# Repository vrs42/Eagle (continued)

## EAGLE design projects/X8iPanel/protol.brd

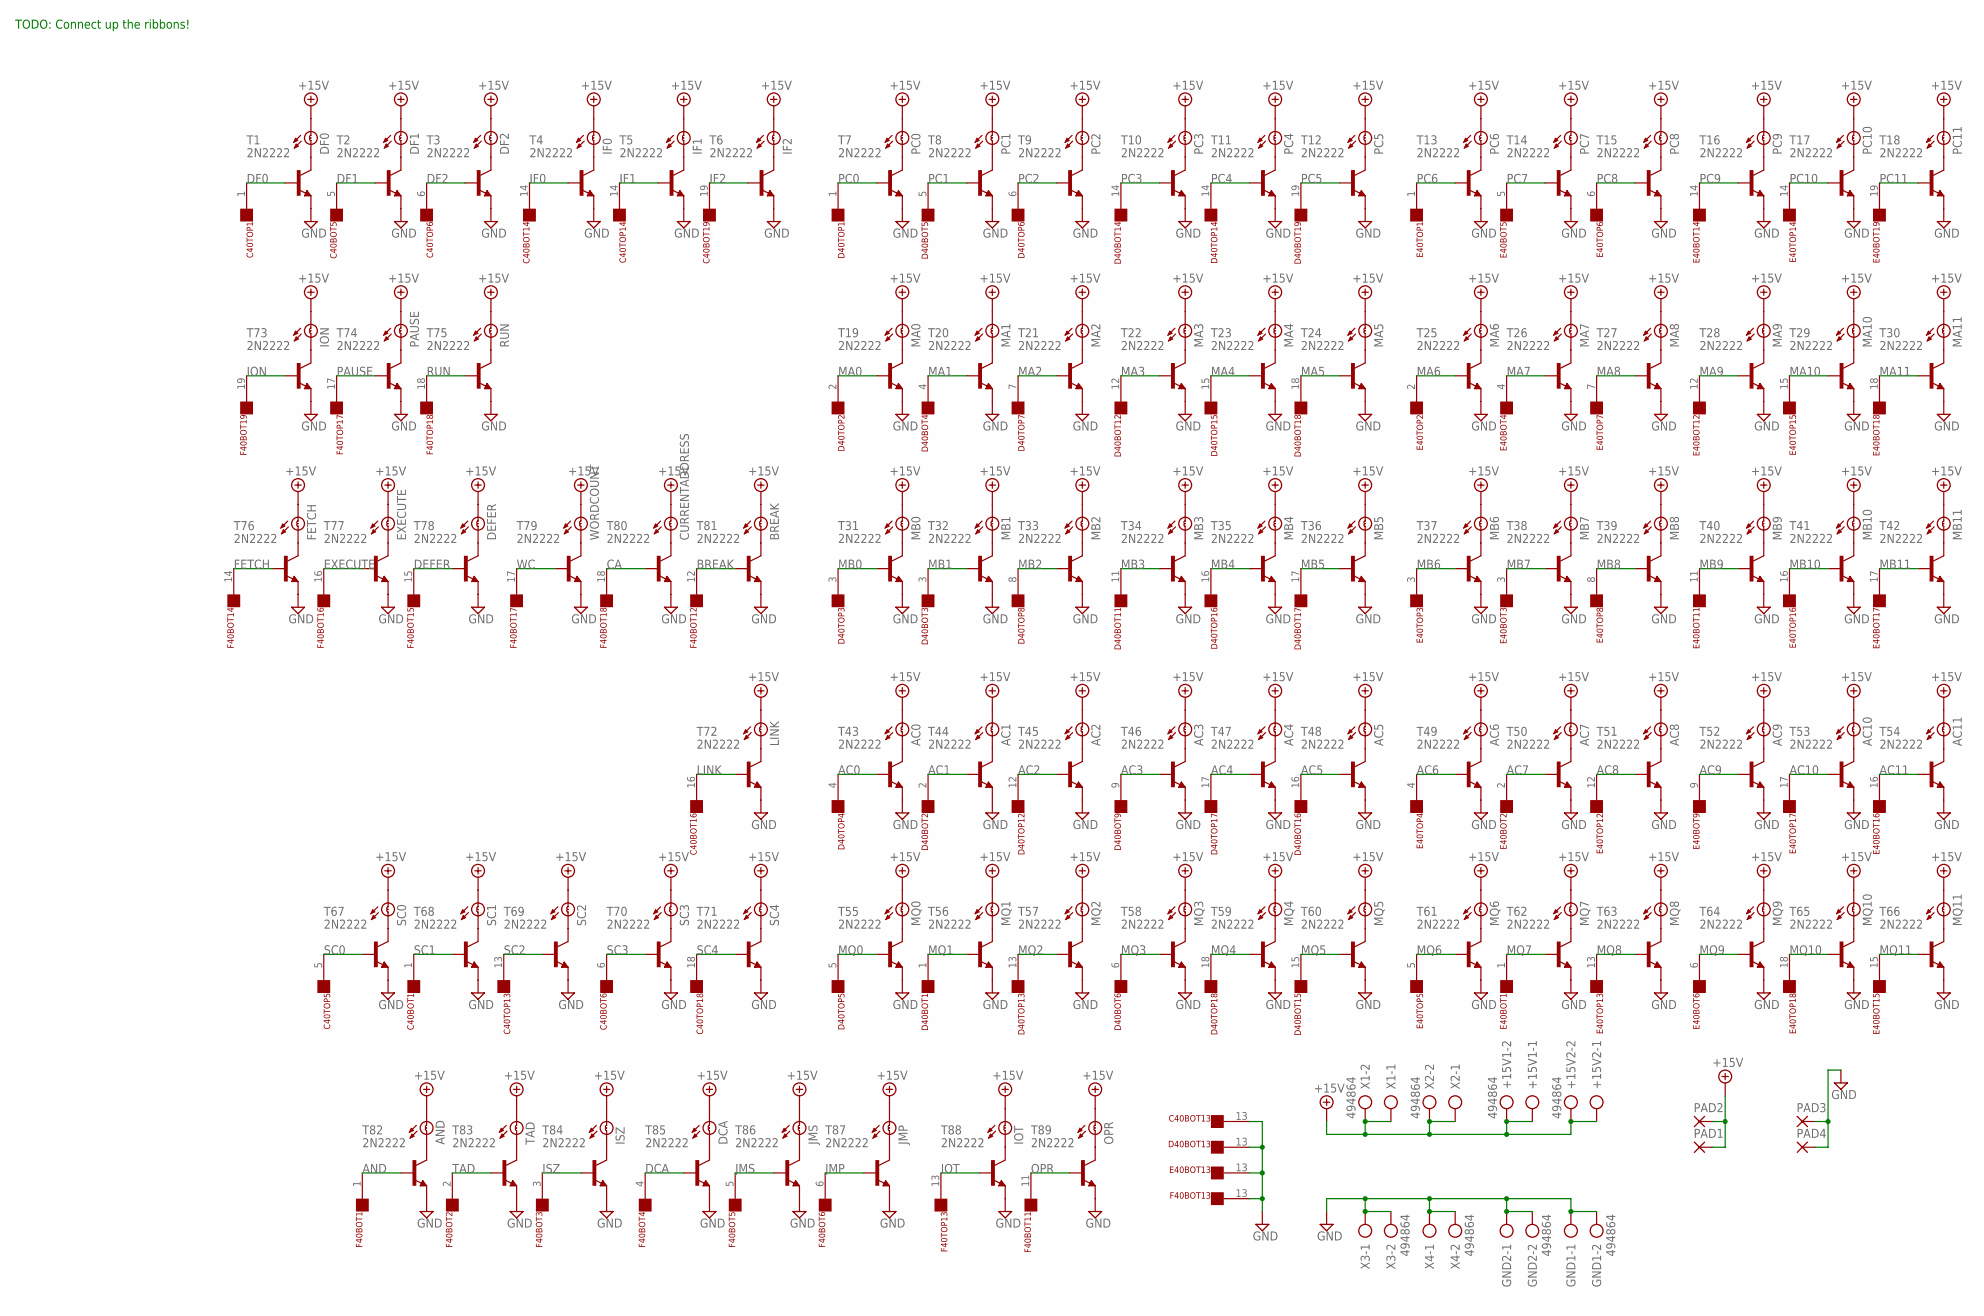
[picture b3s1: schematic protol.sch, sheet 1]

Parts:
+15V1, +15V2: 494864; AK500/2
AC0, AC1, AC2, AC3, AC4, AC5, AC6, AC7, AC8, AC9, AC10, AC11: BULB
AND: BULB
BREAK: BULB
C40BOT, C40TOP: FLEX19
CURRENTADDRESS: BULB
D40BOT, D40TOP: FLEX19
DCA: BULB
DEFER: BULB
DF0, DF1, DF2: BULB
E40BOT, E40TOP: FLEX19
EXECUTE: BULB
F40BOT, F40TOP: FLEX19
FETCH: BULB
GND1, GND2: 494864; AK500/2
IF0, IF1, IF2: BULB
ION: BULB
IOT: BULB
ISZ: BULB
JMP: BULB
JMS: BULB
LINK: BULB
MA0, MA1, MA2, MA3, MA4, MA5, MA6, MA7, MA8, MA9, MA10, MA11: BULB
MB0, MB1, MB2, MB3, MB4, MB5, MB6, MB7, MB8, MB9, MB10, MB11: BULB
MQ0, MQ1, MQ2, MQ3, MQ4, MQ5, MQ6, MQ7, MQ8, MQ9, MQ10, MQ11: BULB
OPR: BULB
PAD1, PAD2, PAD3, PAD4: 2,54/0,8
PAUSE: BULB
PC0, PC1, PC2, PC3, PC4, PC5, PC6, PC7, PC8, PC9, PC10, PC11: BULB
RUN: BULB
SC0, SC1, SC2, SC3, SC4: BULB
T1, T2, T3, T4, T5, T6, T7, T8, T9, T10, T11, T12, T13, T14, T15, T16, T17, T18, T19, T20, T21, T22, T23, T24, T25, T26, T27, T28, T29, T30, T31, T32, T33, T34, T35, T36, T37, T38, T39, T40, T41, T42, T43, T44, T45, T46, T47, T48, T49, T50, T51, T52, T53, T54, T55, T56, T57, T58, T59, T60, T61, T62, T63, T64, T65, T66, T67, T68, T69, T70, T71, T72, T73, T74, T75, T76, T77, T78, T79, T80, T81, T82, T83, T84, T85, T86, T87, T88, T89: 2N2222; TO92
TAD: BULB
WORDCOUNT: BULB
X1, X2, X3, X4: 494864; AK500/2

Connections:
+15V: +15V1.1, +15V1.2, +15V2.1, +15V2.2, AC0.A, AC1.A, AC2.A, AC3.A, AC4.A, AC5.A, AC6.A, AC7.A, AC8.A, AC9.A, AC10.A, AC11.A, AND.A, BREAK.A, CURRENTADDRESS.A, DCA.A, DEFER.A, DF0.A, DF1.A, DF2.A, EXECUTE.A, FETCH.A, IF0.A, IF1.A, IF2.A, ION.A, IOT.A, ISZ.A, JMP.A, JMS.A, LINK.A, MA0.A, MA1.A, MA2.A, MA3.A, MA4.A, MA5.A, MA6.A, MA7.A, MA8.A, MA9.A, MA10.A, MA11.A, MB0.A, MB1.A, MB2.A, MB3.A, MB4.A, MB5.A, MB6.A, MB7.A, MB8.A, MB9.A, MB10.A, MB11.A, MQ0.A, MQ1.A, MQ2.A, MQ3.A, MQ4.A, MQ5.A, MQ6.A, MQ7.A, MQ8.A, MQ9.A, MQ10.A, MQ11.A, OPR.A, PAD1.1, PAD2.1, PAUSE.A, PC0.A, PC1.A, PC2.A, PC3.A, PC4.A, PC5.A, PC6.A, PC7.A, PC8.A, PC9.A, PC10.A, PC11.A, RUN.A, SC0.A, SC1.A, SC2.A, SC3.A, SC4.A, TAD.A, WORDCOUNT.A, X1.1, X1.2, X2.1, X2.2
AC0: D40TOP.4, T43.2 (B); also elsewhere on the board
AC1: D40BOT.2, T44.2 (B); also elsewhere on the board
AC2: D40TOP.12, T45.2 (B); also elsewhere on the board
AC3: D40BOT.9, T46.2 (B); also elsewhere on the board
AC4: D40TOP.17, T47.2 (B); also elsewhere on the board
AC5: D40BOT.16, T48.2 (B); also elsewhere on the board
AC6: E40TOP.4, T49.2 (B); also elsewhere on the board
AC7: E40BOT.2, T50.2 (B); also elsewhere on the board
AC8: E40TOP.12, T51.2 (B); also elsewhere on the board
AC9: E40BOT.9, T52.2 (B); also elsewhere on the board
AC10: E40TOP.17, T53.2 (B); also elsewhere on the board
AC11: E40BOT.16, T54.2 (B); also elsewhere on the board
AND: F40BOT.1, T82.2 (B); also elsewhere on the board
BREAK: F40BOT.12, T81.2 (B); also elsewhere on the board
CA: F40BOT.18, T80.2 (B); also elsewhere on the board
DCA: F40BOT.4, T85.2 (B); also elsewhere on the board
DEFER: F40BOT.15, T78.2 (B); also elsewhere on the board
DF0: C40TOP.1, T1.2 (B); also elsewhere on the board
DF1: C40BOT.5, T2.2 (B); also elsewhere on the board
DF2: C40TOP.6, T3.2 (B); also elsewhere on the board
EXECUTE: F40BOT.16, T77.2 (B); also elsewhere on the board
FETCH: F40BOT.14, T76.2 (B); also elsewhere on the board
GND: C40BOT.13, D40BOT.13, E40BOT.13, F40BOT.13, GND1.1, GND1.2, GND2.1, GND2.2, PAD3.1, PAD4.1, T1.1 (E), T2.1 (E), T3.1 (E), T4.1 (E), T5.1 (E), T6.1 (E), T7.1 (E), T8.1 (E), T9.1 (E), T10.1 (E), T11.1 (E), T12.1 (E), T13.1 (E), T14.1 (E), T15.1 (E), T16.1 (E), T17.1 (E), T18.1 (E), T19.1 (E), T20.1 (E), T21.1 (E), T22.1 (E), T23.1 (E), T24.1 (E), T25.1 (E), T26.1 (E), T27.1 (E), T28.1 (E), T29.1 (E), T30.1 (E), T31.1 (E), T32.1 (E), T33.1 (E), T34.1 (E), T35.1 (E), T36.1 (E), T37.1 (E), T38.1 (E), T39.1 (E), T40.1 (E), T41.1 (E), T42.1 (E), T43.1 (E), T44.1 (E), T45.1 (E), T46.1 (E), T47.1 (E), T48.1 (E), T49.1 (E), T50.1 (E), T51.1 (E), T52.1 (E), T53.1 (E), T54.1 (E), T55.1 (E), T56.1 (E), T57.1 (E), T58.1 (E), T59.1 (E), T60.1 (E), T61.1 (E), T62.1 (E), T63.1 (E), T64.1 (E), T65.1 (E), T66.1 (E), T67.1 (E), T68.1 (E), T69.1 (E), T70.1 (E), T71.1 (E), T72.1 (E), T73.1 (E), T74.1 (E), T75.1 (E), T76.1 (E), T77.1 (E), T78.1 (E), T79.1 (E), T80.1 (E), T81.1 (E), T82.1 (E), T83.1 (E), T84.1 (E), T85.1 (E), T86.1 (E), T87.1 (E), T88.1 (E), T89.1 (E), X3.1, X3.2, X4.1, X4.2; also elsewhere on the board
IF0: C40BOT.14, T4.2 (B); also elsewhere on the board
IF1: C40TOP.14, T5.2 (B); also elsewhere on the board
IF2: C40BOT.19, T6.2 (B); also elsewhere on the board
ION: F40BOT.19, T73.2 (B); also elsewhere on the board
IOT: F40TOP.13, T88.2 (B); also elsewhere on the board
ISZ: F40BOT.3, T84.2 (B); also elsewhere on the board
JMP: F40BOT.6, T87.2 (B); also elsewhere on the board
JMS: F40BOT.5, T86.2 (B); also elsewhere on the board
LINK: C40BOT.16, T72.2 (B); also elsewhere on the board
MA0: D40TOP.2, T19.2 (B); also elsewhere on the board
MA1: D40BOT.4, T20.2 (B); also elsewhere on the board
MA2: D40TOP.7, T21.2 (B); also elsewhere on the board
MA3: D40BOT.12, T22.2 (B); also elsewhere on the board
MA4: D40TOP.15, T23.2 (B); also elsewhere on the board
MA5: D40BOT.18, T24.2 (B); also elsewhere on the board
MA6: E40TOP.2, T25.2 (B); also elsewhere on the board
MA7: E40BOT.4, T26.2 (B); also elsewhere on the board
MA8: E40TOP.7, T27.2 (B); also elsewhere on the board
MA9: E40BOT.12, T28.2 (B); also elsewhere on the board
MA10: E40TOP.15, T29.2 (B); also elsewhere on the board
MA11: E40BOT.18, T30.2 (B); also elsewhere on the board
MB0: D40TOP.3, T31.2 (B); also elsewhere on the board
MB1: D40BOT.3, T32.2 (B); also elsewhere on the board
MB2: D40TOP.8, T33.2 (B); also elsewhere on the board
MB3: D40BOT.11, T34.2 (B); also elsewhere on the board
MB4: D40TOP.16, T35.2 (B); also elsewhere on the board
MB5: D40BOT.17, T36.2 (B); also elsewhere on the board
MB6: E40TOP.3, T37.2 (B); also elsewhere on the board
MB7: E40BOT.3, T38.2 (B); also elsewhere on the board
MB8: E40TOP.8, T39.2 (B); also elsewhere on the board
MB9: E40BOT.11, T40.2 (B); also elsewhere on the board
MB10: E40TOP.16, T41.2 (B); also elsewhere on the board
MB11: E40BOT.17, T42.2 (B); also elsewhere on the board
MQ0: D40TOP.5, T55.2 (B); also elsewhere on the board
MQ1: D40BOT.1, T56.2 (B); also elsewhere on the board
MQ2: D40TOP.13, T57.2 (B); also elsewhere on the board
MQ3: D40BOT.6, T58.2 (B); also elsewhere on the board
MQ4: D40TOP.18, T59.2 (B); also elsewhere on the board
MQ5: D40BOT.15, T60.2 (B); also elsewhere on the board
MQ6: E40TOP.5, T61.2 (B); also elsewhere on the board
MQ7: E40BOT.1, T62.2 (B); also elsewhere on the board
MQ8: E40TOP.13, T63.2 (B); also elsewhere on the board
MQ9: E40BOT.6, T64.2 (B); also elsewhere on the board
MQ10: E40TOP.18, T65.2 (B); also elsewhere on the board
MQ11: E40BOT.15, T66.2 (B); also elsewhere on the board
unnamed: DF0.B, T1.3 (C)
unnamed: DF1.B, T2.3 (C)
unnamed: DF2.B, T3.3 (C)
unnamed: IF0.B, T4.3 (C)
unnamed: IF1.B, T5.3 (C)
unnamed: IF2.B, T6.3 (C)
unnamed: PC0.B, T7.3 (C)
unnamed: PC1.B, T8.3 (C)
unnamed: PC2.B, T9.3 (C)
unnamed: PC3.B, T10.3 (C)
unnamed: PC4.B, T11.3 (C)
unnamed: PC5.B, T12.3 (C)
unnamed: PC6.B, T13.3 (C)
unnamed: PC7.B, T14.3 (C)
unnamed: PC8.B, T15.3 (C)
unnamed: PC9.B, T16.3 (C)
unnamed: PC10.B, T17.3 (C)
unnamed: PC11.B, T18.3 (C)
unnamed: MA0.B, T19.3 (C)
unnamed: MA1.B, T20.3 (C)
unnamed: MA2.B, T21.3 (C)
unnamed: MA3.B, T22.3 (C)
unnamed: MA4.B, T23.3 (C)
unnamed: MA5.B, T24.3 (C)
unnamed: MA6.B, T25.3 (C)
unnamed: MA7.B, T26.3 (C)
unnamed: MA8.B, T27.3 (C)
unnamed: MA9.B, T28.3 (C)
unnamed: MA10.B, T29.3 (C)
unnamed: MA11.B, T30.3 (C)
unnamed: MB0.B, T31.3 (C)
unnamed: MB1.B, T32.3 (C)
unnamed: MB2.B, T33.3 (C)
unnamed: MB3.B, T34.3 (C)
unnamed: MB4.B, T35.3 (C)
unnamed: MB5.B, T36.3 (C)
unnamed: MB6.B, T37.3 (C)
unnamed: MB7.B, T38.3 (C)
unnamed: MB8.B, T39.3 (C)
unnamed: MB9.B, T40.3 (C)
unnamed: MB10.B, T41.3 (C)
unnamed: MB11.B, T42.3 (C)
unnamed: AC0.B, T43.3 (C)
unnamed: AC1.B, T44.3 (C)
unnamed: AC2.B, T45.3 (C)
unnamed: AC3.B, T46.3 (C)
unnamed: AC4.B, T47.3 (C)
unnamed: AC5.B, T48.3 (C)
unnamed: AC6.B, T49.3 (C)
unnamed: AC7.B, T50.3 (C)
unnamed: AC8.B, T51.3 (C)
unnamed: AC9.B, T52.3 (C)
unnamed: AC10.B, T53.3 (C)
unnamed: AC11.B, T54.3 (C)
unnamed: MQ0.B, T55.3 (C)
unnamed: MQ1.B, T56.3 (C)
unnamed: MQ2.B, T57.3 (C)
unnamed: MQ3.B, T58.3 (C)
unnamed: MQ4.B, T59.3 (C)
unnamed: MQ5.B, T60.3 (C)
unnamed: MQ6.B, T61.3 (C)
unnamed: MQ7.B, T62.3 (C)
unnamed: MQ8.B, T63.3 (C)
unnamed: MQ9.B, T64.3 (C)
unnamed: MQ10.B, T65.3 (C)
unnamed: MQ11.B, T66.3 (C)
unnamed: SC0.B, T67.3 (C)
unnamed: SC1.B, T68.3 (C)
unnamed: SC2.B, T69.3 (C)
unnamed: SC3.B, T70.3 (C)
unnamed: SC4.B, T71.3 (C)
unnamed: LINK.B, T72.3 (C)
unnamed: ION.B, T73.3 (C)
unnamed: PAUSE.B, T74.3 (C)
unnamed: RUN.B, T75.3 (C)
unnamed: FETCH.B, T76.3 (C)
unnamed: EXECUTE.B, T77.3 (C)
unnamed: DEFER.B, T78.3 (C)
unnamed: T79.3 (C), WORDCOUNT.B
unnamed: CURRENTADDRESS.B, T80.3 (C)
unnamed: BREAK.B, T81.3 (C)
unnamed: AND.B, T82.3 (C)
unnamed: T83.3 (C), TAD.B
unnamed: ISZ.B, T84.3 (C)
unnamed: DCA.B, T85.3 (C)
unnamed: JMS.B, T86.3 (C)
unnamed: JMP.B, T87.3 (C)
unnamed: IOT.B, T88.3 (C)
unnamed: OPR.B, T89.3 (C)
OPR: F40BOT.11, T89.2 (B); also elsewhere on the board
PAUSE: F40TOP.17, T74.2 (B); also elsewhere on the board
PC0: D40TOP.1, T7.2 (B); also elsewhere on the board
PC1: D40BOT.5, T8.2 (B); also elsewhere on the board
PC2: D40TOP.6, T9.2 (B); also elsewhere on the board
PC3: D40BOT.14, T10.2 (B); also elsewhere on the board
PC4: D40TOP.14, T11.2 (B); also elsewhere on the board
PC5: D40BOT.19, T12.2 (B); also elsewhere on the board
PC6: E40TOP.1, T13.2 (B); also elsewhere on the board
PC7: E40BOT.5, T14.2 (B); also elsewhere on the board
PC8: E40TOP.6, T15.2 (B); also elsewhere on the board
PC9: E40BOT.14, T16.2 (B); also elsewhere on the board
PC10: E40TOP.14, T17.2 (B); also elsewhere on the board
PC11: E40BOT.19, T18.2 (B); also elsewhere on the board
RUN: F40TOP.18, T75.2 (B); also elsewhere on the board
SC0: C40TOP.5, T67.2 (B); also elsewhere on the board
SC1: C40BOT.1, T68.2 (B); also elsewhere on the board
SC2: C40TOP.13, T69.2 (B); also elsewhere on the board
SC3: C40BOT.6, T70.2 (B); also elsewhere on the board
SC4: C40TOP.18, T71.2 (B); also elsewhere on the board
TAD: F40BOT.2, T83.2 (B); also elsewhere on the board
WC: F40BOT.17, T79.2 (B); also elsewhere on the board

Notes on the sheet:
TODO: Connect up the ribbons!

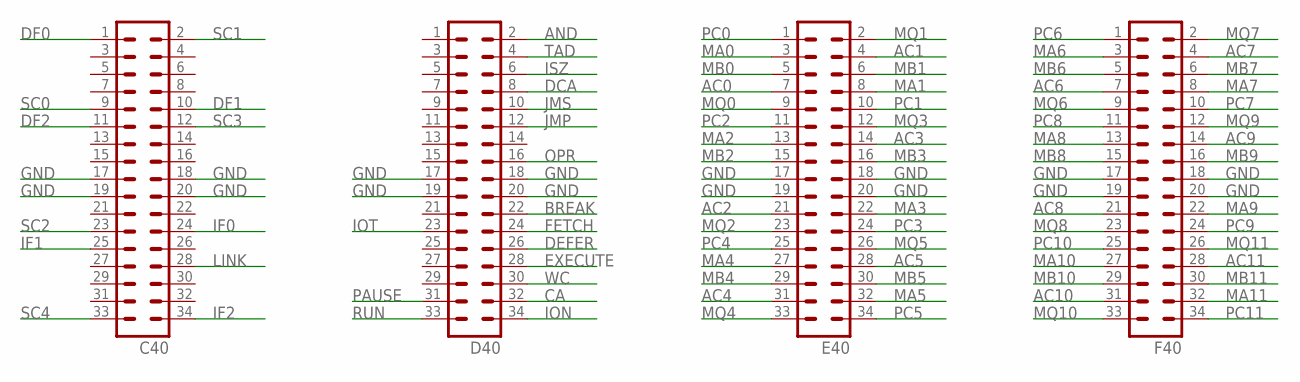
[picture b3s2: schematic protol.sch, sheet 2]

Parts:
C40: MA17-2
D40: MA17-2
E40: MA17-2
F40: MA17-2

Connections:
AC0: E40.7; also elsewhere on the board
AC1: E40.4; also elsewhere on the board
AC2: E40.21; also elsewhere on the board
AC3: E40.14; also elsewhere on the board
AC4: E40.31; also elsewhere on the board
AC5: E40.28; also elsewhere on the board
AC6: F40.7; also elsewhere on the board
AC7: F40.4; also elsewhere on the board
AC8: F40.21; also elsewhere on the board
AC9: F40.14; also elsewhere on the board
AC10: F40.31; also elsewhere on the board
AC11: F40.28; also elsewhere on the board
AND: D40.2; also elsewhere on the board
BREAK: D40.22; also elsewhere on the board
CA: D40.32; also elsewhere on the board
DCA: D40.8; also elsewhere on the board
DEFER: D40.26; also elsewhere on the board
DF0: C40.1; also elsewhere on the board
DF1: C40.10; also elsewhere on the board
DF2: C40.11; also elsewhere on the board
EXECUTE: D40.28; also elsewhere on the board
FETCH: D40.24; also elsewhere on the board
GND: C40.17, C40.18, C40.19, C40.20, D40.17, D40.18, D40.19, D40.20, E40.17, E40.18, E40.19, E40.20, F40.17, F40.18, F40.19, F40.20; also elsewhere on the board
IF0: C40.24; also elsewhere on the board
IF1: C40.25; also elsewhere on the board
IF2: C40.34; also elsewhere on the board
ION: D40.34; also elsewhere on the board
IOT: D40.23; also elsewhere on the board
ISZ: D40.6; also elsewhere on the board
JMP: D40.12; also elsewhere on the board
JMS: D40.10; also elsewhere on the board
LINK: C40.28; also elsewhere on the board
MA0: E40.3; also elsewhere on the board
MA1: E40.8; also elsewhere on the board
MA2: E40.13; also elsewhere on the board
MA3: E40.22; also elsewhere on the board
MA4: E40.27; also elsewhere on the board
MA5: E40.32; also elsewhere on the board
MA6: F40.3; also elsewhere on the board
MA7: F40.8; also elsewhere on the board
MA8: F40.13; also elsewhere on the board
MA9: F40.22; also elsewhere on the board
MA10: F40.27; also elsewhere on the board
MA11: F40.32; also elsewhere on the board
MB0: E40.5; also elsewhere on the board
MB1: E40.6; also elsewhere on the board
MB2: E40.15; also elsewhere on the board
MB3: E40.16; also elsewhere on the board
MB4: E40.29; also elsewhere on the board
MB5: E40.30; also elsewhere on the board
MB6: F40.5; also elsewhere on the board
MB7: F40.6; also elsewhere on the board
MB8: F40.15; also elsewhere on the board
MB9: F40.16; also elsewhere on the board
MB10: F40.29; also elsewhere on the board
MB11: F40.30; also elsewhere on the board
MQ0: E40.9; also elsewhere on the board
MQ1: E40.2; also elsewhere on the board
MQ2: E40.23; also elsewhere on the board
MQ3: E40.12; also elsewhere on the board
MQ4: E40.33; also elsewhere on the board
MQ5: E40.26; also elsewhere on the board
MQ6: F40.9; also elsewhere on the board
MQ7: F40.2; also elsewhere on the board
MQ8: F40.23; also elsewhere on the board
MQ9: F40.12; also elsewhere on the board
MQ10: F40.33; also elsewhere on the board
MQ11: F40.26; also elsewhere on the board
OPR: D40.16; also elsewhere on the board
PAUSE: D40.31; also elsewhere on the board
PC0: E40.1; also elsewhere on the board
PC1: E40.10; also elsewhere on the board
PC2: E40.11; also elsewhere on the board
PC3: E40.24; also elsewhere on the board
PC4: E40.25; also elsewhere on the board
PC5: E40.34; also elsewhere on the board
PC6: F40.1; also elsewhere on the board
PC7: F40.10; also elsewhere on the board
PC8: F40.11; also elsewhere on the board
PC9: F40.24; also elsewhere on the board
PC10: F40.25; also elsewhere on the board
PC11: F40.34; also elsewhere on the board
RUN: D40.33; also elsewhere on the board
SC0: C40.9; also elsewhere on the board
SC1: C40.2; also elsewhere on the board
SC2: C40.23; also elsewhere on the board
SC3: C40.12; also elsewhere on the board
SC4: C40.33; also elsewhere on the board
TAD: D40.4; also elsewhere on the board
WC: D40.30; also elsewhere on the board

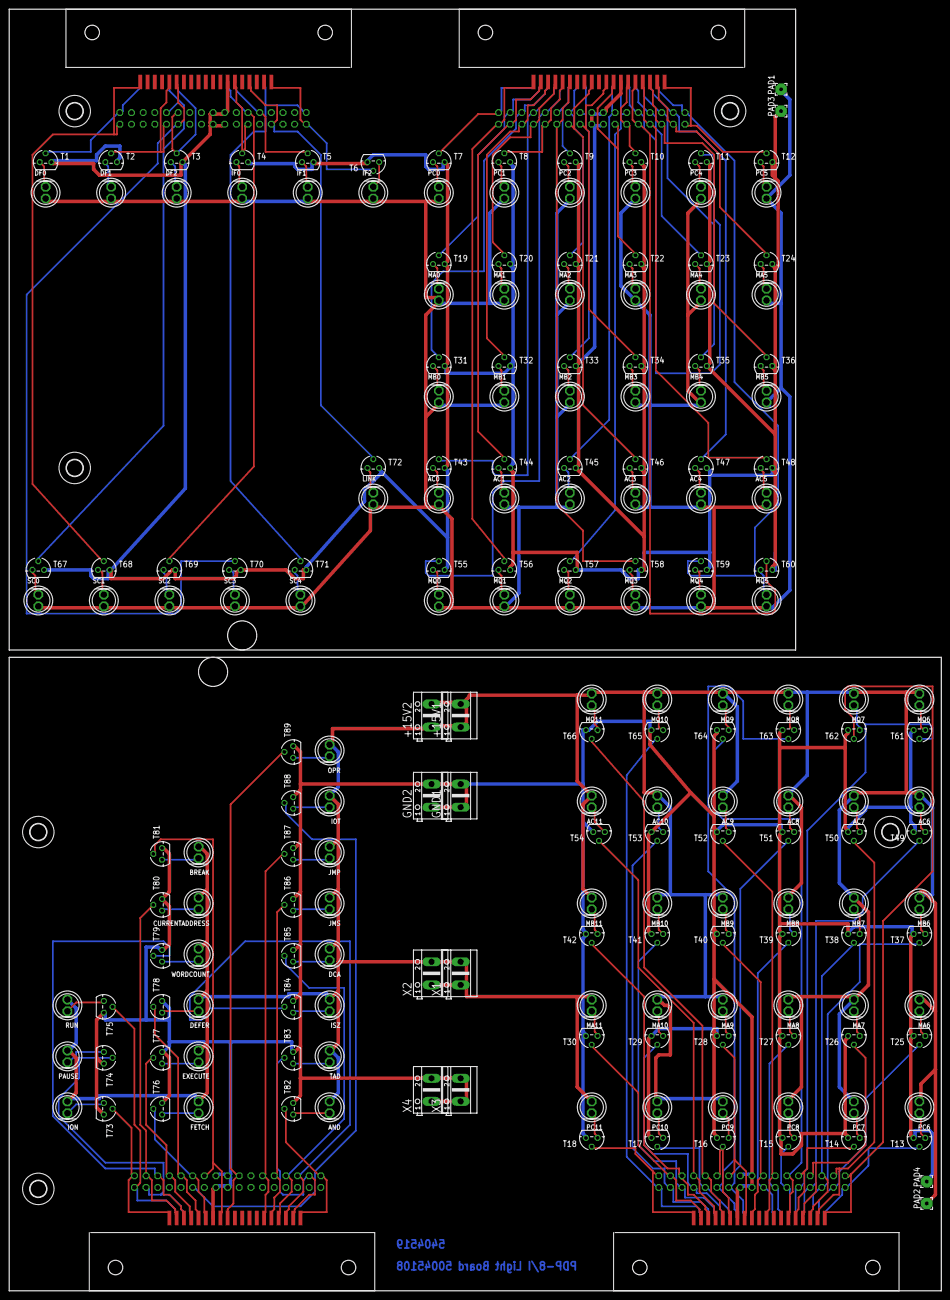
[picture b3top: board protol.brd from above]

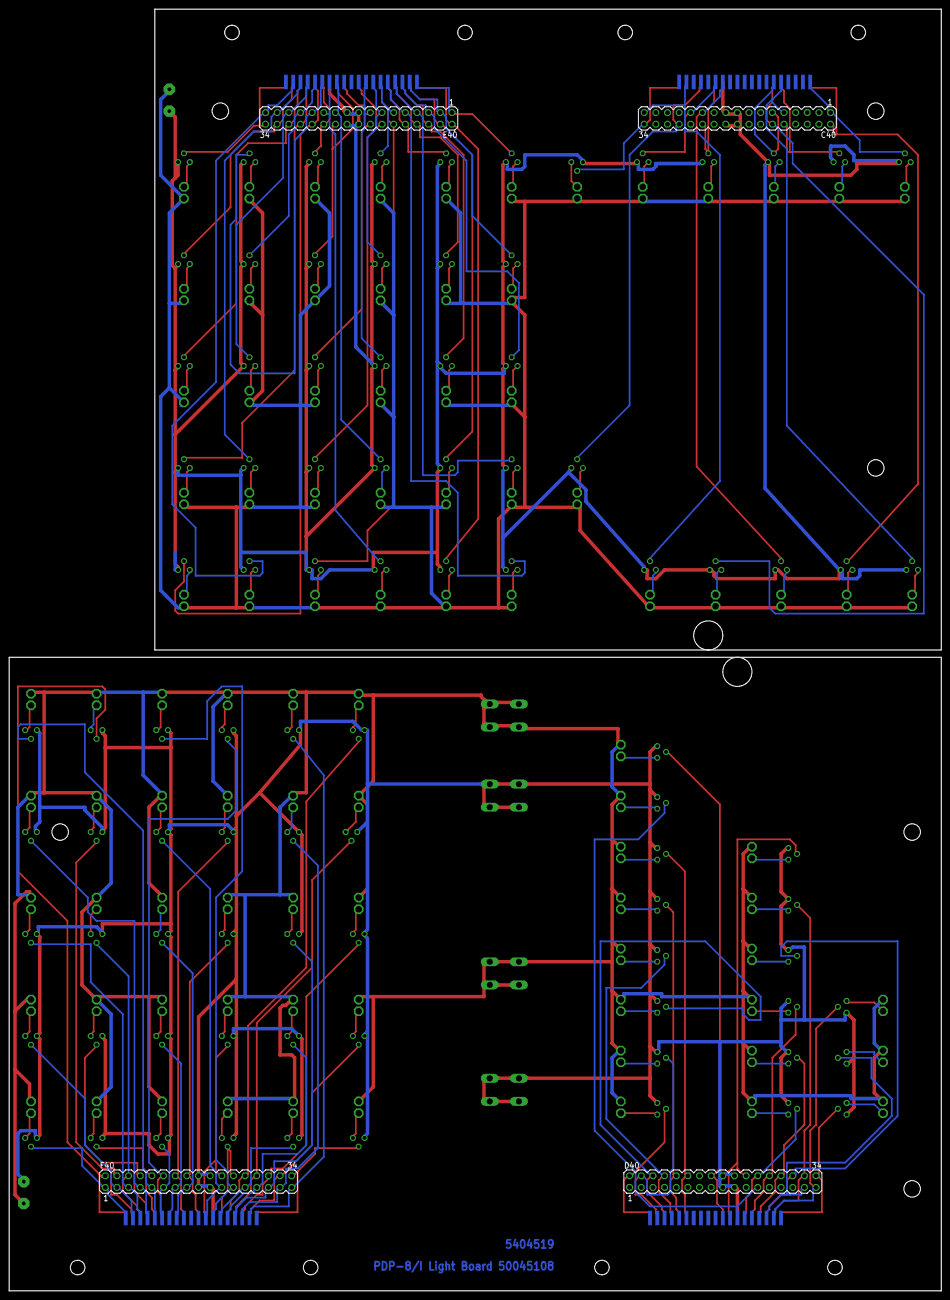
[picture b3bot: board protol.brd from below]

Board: 2 copper layers, 203.2 x 279.4 mm, 212 parts (8 on the bottom side), 180 nets.

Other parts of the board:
U$1, U$2, U$3, U$4: STRAIN-RELIEF
U$5, U$6, U$7, U$8, U$9, U$11: 3,6

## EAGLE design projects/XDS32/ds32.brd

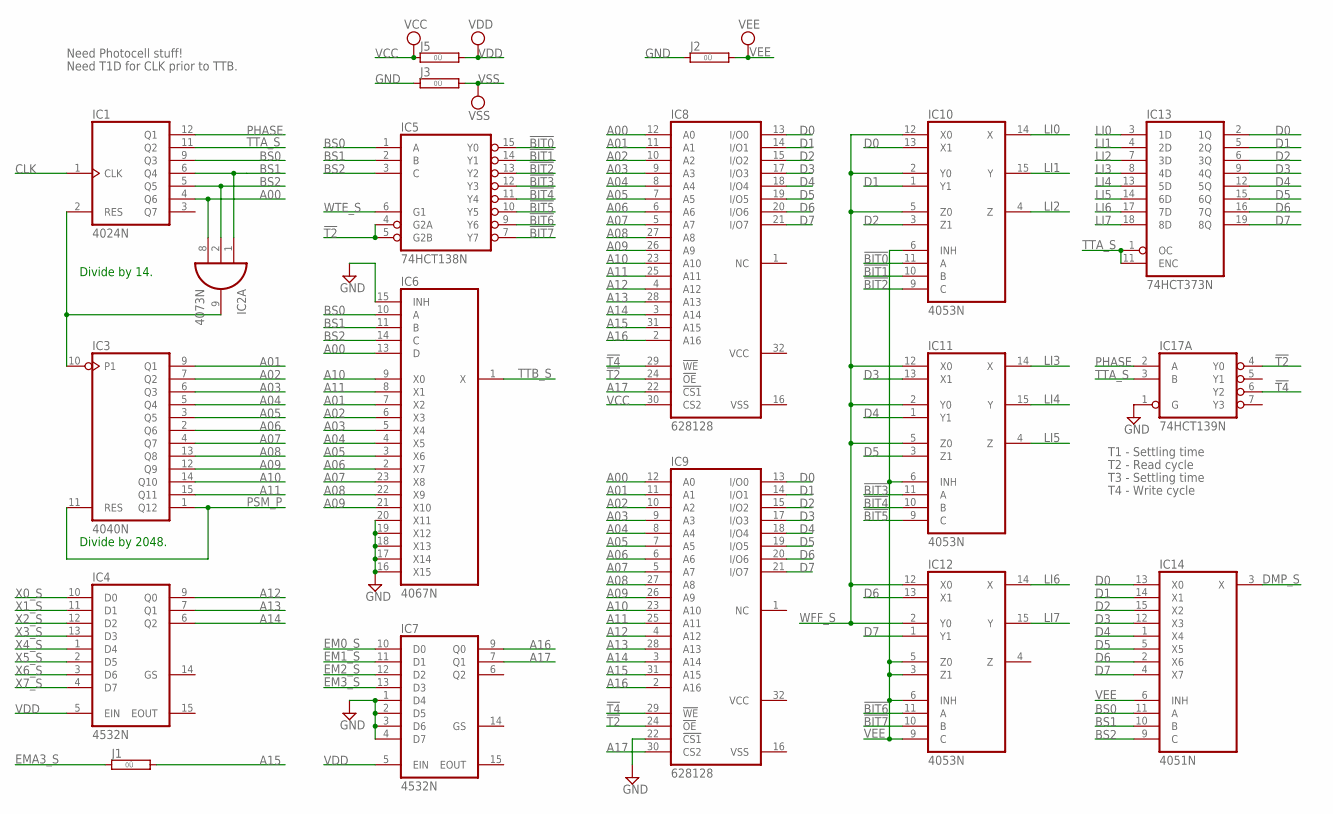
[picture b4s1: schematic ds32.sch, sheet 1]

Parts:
IC1: 4024N; DIL14
IC2: 4073N; DIL14
IC3: 4040N; DIL16
IC4, IC7: 4532N; DIL16
IC5: 74HCT138N; DIL16
IC6: 4067N; DIL24-6
IC8, IC9: 628128; DIL32
IC10, IC11, IC12: 4053N; DIL16
IC13: 74HCT373N; DIL20
IC14: 4051N; DIL16
IC17: 74HCT139N; DIL16
J1, J2, J3, J5: 0R; 0R/10

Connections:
!BIT0: IC5.15 (Y0), IC10.11 (A)
!BIT1: IC5.14 (Y1), IC10.10 (B)
!BIT2: IC5.13 (Y2), IC10.9 (C)
!BIT3: IC5.12 (Y3), IC11.11 (A)
!BIT4: IC5.11 (Y4), IC11.10 (B)
!BIT5: IC5.10 (Y5), IC11.9 (C)
!BIT6: IC5.9 (Y6), IC12.11 (A)
!BIT7: IC5.7 (Y7), IC12.10 (B)
!T2: IC5.4 (G2A), IC5.5 (G2B), IC8.24 (!OE), IC9.24 (!OE), IC17.4 (Y0)
!T4: IC8.29 (!WE), IC9.29 (!WE), IC17.6 (Y2)
A00: IC1.4 (Q6), IC2.8 (I2), IC6.13 (D), IC8.12 (A0), IC9.12 (A0)
A01: IC3.9 (Q1), IC6.7 (X2), IC8.11 (A1), IC9.11 (A1)
A02: IC3.7 (Q2), IC6.6 (X3), IC8.10 (A2), IC9.10 (A2)
A03: IC3.6 (Q3), IC6.5 (X4), IC8.9 (A3), IC9.9 (A3)
A04: IC3.5 (Q4), IC6.4 (X5), IC8.8 (A4), IC9.8 (A4)
A05: IC3.3 (Q5), IC6.3 (X6), IC8.7 (A5), IC9.7 (A5)
A06: IC3.2 (Q6), IC6.2 (X7), IC8.6 (A6), IC9.6 (A6)
A07: IC3.4 (Q7), IC6.23 (X8), IC8.5 (A7), IC9.5 (A7)
A08: IC3.13 (Q8), IC6.22 (X9), IC8.27 (A8), IC9.27 (A8)
A09: IC3.12 (Q9), IC6.21 (X10), IC8.26 (A9), IC9.26 (A9)
A10: IC3.14 (Q10), IC6.9 (X0), IC8.23 (A10), IC9.23 (A10)
A11: IC3.15 (Q11), IC6.8 (X1), IC8.25 (A11), IC9.25 (A11)
A12: IC4.9 (Q0), IC8.4 (A12), IC9.4 (A12)
A13: IC4.7 (Q1), IC8.28 (A13), IC9.28 (A13)
A14: IC4.6 (Q2), IC8.3 (A14), IC9.3 (A14)
A15: IC8.31 (A15), IC9.31 (A15), J1.2
A16: IC7.9 (Q0), IC8.2 (A16), IC9.2 (A16)
A17: IC7.7 (Q1), IC8.22 (!CS1), IC9.30 (CS2)
BS0: IC1.9 (Q3), IC5.1 (A), IC6.10 (A), IC14.11 (A)
BS1: IC1.6 (Q4), IC2.1 (I0), IC5.2 (B), IC6.11 (B), IC14.10 (B)
BS2: IC1.5 (Q5), IC2.2 (I1), IC5.3 (C), IC6.14 (C), IC14.9 (C)
CLK: IC1.1 (CLK); also elsewhere on the board
D0: IC8.13 (I/O0), IC9.13 (I/O0), IC10.13 (X1), IC13.2 (1Q), IC14.13 (X0)
D1: IC8.14 (I/O1), IC9.14 (I/O1), IC10.1 (Y1), IC13.5 (2Q), IC14.14 (X1)
D2: IC8.15 (I/O2), IC9.15 (I/O2), IC10.3 (Z1), IC13.6 (3Q), IC14.15 (X2)
D3: IC8.17 (I/O3), IC9.17 (I/O3), IC11.13 (X1), IC13.9 (4Q), IC14.12 (X3)
D4: IC8.18 (I/O4), IC9.18 (I/O4), IC11.1 (Y1), IC13.12 (5Q), IC14.1 (X4)
D5: IC8.19 (I/O5), IC9.19 (I/O5), IC11.3 (Z1), IC13.15 (6Q), IC14.5 (X5)
D6: IC8.20 (I/O6), IC9.20 (I/O6), IC12.13 (X1), IC13.16 (7Q), IC14.2 (X6)
D7: IC8.21 (I/O7), IC9.21 (I/O7), IC12.1 (Y1), IC13.19 (8Q), IC14.4 (X7)
DMP_S: IC14.3 (X); also elsewhere on the board
EM0_S: IC7.10 (D0); also elsewhere on the board
EM1_S: IC7.11 (D1); also elsewhere on the board
EM2_S: IC7.12 (D2); also elsewhere on the board
EM3_S: IC7.13 (D3); also elsewhere on the board
EMA3_S: J1.1; also elsewhere on the board
GND: IC5.8 (GND), IC6.15 (INH), IC6.16 (X15), IC6.17 (X14), IC6.18 (X13), IC6.19 (X12), IC6.20 (X11), IC7.1 (D4), IC7.2 (D5), IC7.3 (D6), IC7.4 (D7), IC9.22 (!CS1), IC10.8 (GND), IC11.8 (GND), IC12.8 (GND), IC13.10 (GND), IC14.8 (GND), IC17.1 (G), IC17.8 (GND), J2.1, J3.1; also elsewhere on the board
LI0: IC10.14 (X), IC13.3 (1D)
LI1: IC10.15 (Y), IC13.4 (2D)
LI2: IC10.4 (Z), IC13.7 (3D)
LI3: IC11.14 (X), IC13.8 (4D)
LI4: IC11.15 (Y), IC13.13 (5D)
LI5: IC11.4 (Z), IC13.14 (6D)
LI6: IC12.14 (X), IC13.17 (7D)
LI7: IC12.15 (Y), IC13.18 (8D)
unnamed: IC1.2 (RES), IC2.9 (O), IC3.10 (P1)
PHASE: IC1.12 (Q1), IC17.2 (A)
PSM_P: IC3.1 (Q12), IC3.11 (RES); also elsewhere on the board
TTA_S: IC1.11 (Q2), IC13.1 (OC), IC13.11 (ENC), IC17.3 (B); also elsewhere on the board
TTB_S: IC6.1 (X); also elsewhere on the board
VCC: IC5.16 (VCC), IC8.30 (CS2), IC8.32 (VCC), IC9.32 (VCC), IC10.16 (VCC), IC11.16 (VCC), IC12.16 (VCC), IC13.20 (VCC), IC14.16 (VCC), IC17.16 (VCC), J5.1; also elsewhere on the board
VDD: IC1.14 (VDD), IC2.14 (VDD), IC3.16 (VDD), IC4.5 (EIN), IC4.16 (VDD), IC6.24 (VDD), IC7.5 (EIN), IC7.16 (VDD), J5.2
VEE: IC10.6 (INH), IC10.7 (VEE), IC11.6 (INH), IC11.7 (VEE), IC12.3 (Z1), IC12.5 (Z0), IC12.6 (INH), IC12.7 (VEE), IC12.9 (C), IC14.6 (INH), IC14.7 (VEE), J2.2
VSS: IC1.7 (VSS), IC2.7 (VSS), IC3.8 (VSS), IC4.8 (VSS), IC6.12 (VSS), IC7.8 (VSS), IC8.16 (VSS), IC9.16 (VSS), J3.2
WFF_S: IC10.2 (Y0), IC10.5 (Z0), IC10.12 (X0), IC11.2 (Y0), IC11.5 (Z0), IC11.12 (X0), IC12.2 (Y0), IC12.12 (X0); also elsewhere on the board
WTE_S: IC5.6 (G1); also elsewhere on the board
X0_S: IC4.10 (D0); also elsewhere on the board
X1_S: IC4.11 (D1); also elsewhere on the board
X2_S: IC4.12 (D2); also elsewhere on the board
X3_S: IC4.13 (D3); also elsewhere on the board
X4_S: IC4.1 (D4); also elsewhere on the board
X5_S: IC4.2 (D5); also elsewhere on the board
X6_S: IC4.3 (D6); also elsewhere on the board
X7_S: IC4.4 (D7); also elsewhere on the board

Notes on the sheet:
Divide by 14.
Divide by 2048.
T1 - Settling time
T2 - Read cycle
T3 - Settling time
T4 - Write cycle
Need T1D for CLK prior to TTB.
Need Photocell stuff!

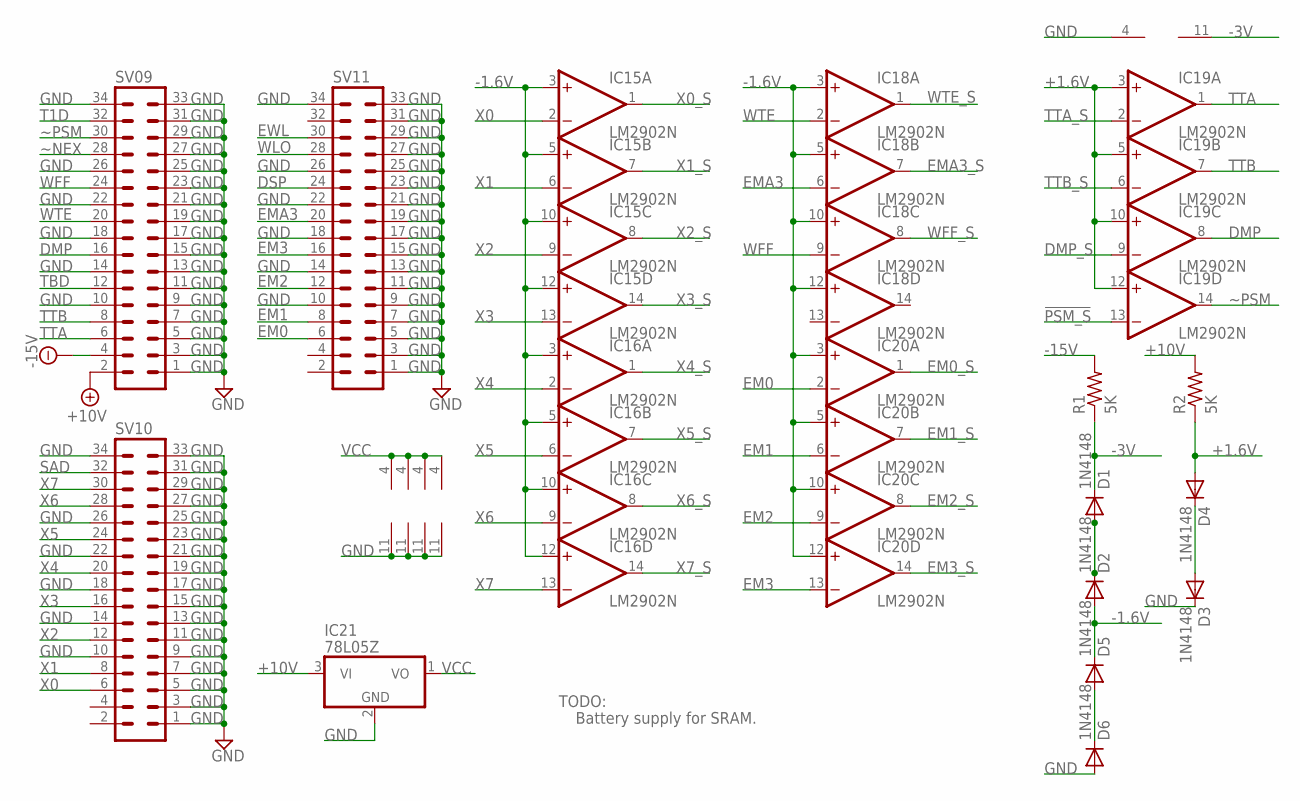
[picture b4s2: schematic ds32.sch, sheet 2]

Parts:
D1, D2, D3, D4, D5, D6: 1N4148; DO35-10
IC15, IC16, IC18, IC19, IC20: LM2902N; DIL14
IC21: 78L05Z; TO92
R1, R2: 5K; 0207/10
SV09, SV10, SV11: MA17-2

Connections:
!PSM_S: IC19.13 (-IN); also elsewhere on the board
+1.6V: D4.A, IC19.3 (+IN), IC19.5 (+IN), IC19.10 (+IN), IC19.12 (+IN), R2.1
+10V: IC21.3 (VI), R2.2, SV09.2
-1.6V: D2.A, D5.C, IC15.3 (+IN), IC15.5 (+IN), IC15.10 (+IN), IC15.12 (+IN), IC16.3 (+IN), IC16.5 (+IN), IC16.10 (+IN), IC16.12 (+IN), IC18.3 (+IN), IC18.5 (+IN), IC18.10 (+IN), IC18.12 (+IN), IC20.3 (+IN), IC20.5 (+IN), IC20.10 (+IN), IC20.12 (+IN)
-3V: D1.C, IC19.11 (V-), R1.1; also elsewhere on the board
-15V: R1.2, SV09.4
DMP: IC19.8 (OUT), SV09.16
DMP_S: IC19.9 (-IN); also elsewhere on the board
DSP: SV11.24
EM0: IC20.2 (-IN), SV11.6
EM0_S: IC20.1 (OUT); also elsewhere on the board
EM1: IC20.6 (-IN), SV11.8
EM1_S: IC20.7 (OUT); also elsewhere on the board
EM2: IC20.9 (-IN), SV11.12
EM2_S: IC20.8 (OUT); also elsewhere on the board
EM3: IC20.13 (-IN), SV11.16
EM3_S: IC20.14 (OUT); also elsewhere on the board
EMA3: IC18.6 (-IN), SV11.20
EMA3_S: IC18.7 (OUT); also elsewhere on the board
EWL: SV11.30
GND: D3.C, D6.A, IC15.11 (V-), IC16.11 (V-), IC18.11 (V-), IC19.4 (V+), IC20.11 (V-), IC21.2 (GND), SV09.1, SV09.3, SV09.5, SV09.7, SV09.9, SV09.10, SV09.11, SV09.13, SV09.14, SV09.15, SV09.17, SV09.18, SV09.19, SV09.21, SV09.22, SV09.23, SV09.25, SV09.26, SV09.27, SV09.29, SV09.31, SV09.33, SV09.34, SV10.1, SV10.3, SV10.5, SV10.7, SV10.9, SV10.10, SV10.11, SV10.13, SV10.14, SV10.15, SV10.17, SV10.18, SV10.19, SV10.21, SV10.22, SV10.23, SV10.25, SV10.26, SV10.27, SV10.29, SV10.31, SV10.33, SV10.34, SV11.1, SV11.3, SV11.5, SV11.7, SV11.9, SV11.10, SV11.11, SV11.13, SV11.14, SV11.15, SV11.17, SV11.18, SV11.19, SV11.21, SV11.22, SV11.23, SV11.25, SV11.26, SV11.27, SV11.29, SV11.31, SV11.33, SV11.34; also elsewhere on the board
unnamed: D1.A, D2.C
unnamed: D3.A, D4.C
unnamed: D5.A, D6.C
SAD: SV10.32
T1D: SV09.32
TBD: SV09.12
TTA: IC19.1 (OUT), SV09.6
TTA_S: IC19.2 (-IN); also elsewhere on the board
TTB: IC19.7 (OUT), SV09.8
TTB_S: IC19.6 (-IN); also elsewhere on the board
VCC: IC15.4 (V+), IC16.4 (V+), IC18.4 (V+), IC20.4 (V+), IC21.1 (VO); also elsewhere on the board
WFF: IC18.9 (-IN), SV09.24
WFF_S: IC18.8 (OUT); also elsewhere on the board
WLO: SV11.28; also elsewhere on the board
WTE: IC18.2 (-IN), SV09.20
WTE_S: IC18.1 (OUT); also elsewhere on the board
X0: IC15.2 (-IN), SV10.6
X0_S: IC15.1 (OUT); also elsewhere on the board
X1: IC15.6 (-IN), SV10.8
X1_S: IC15.7 (OUT); also elsewhere on the board
X2: IC15.9 (-IN), SV10.12
X2_S: IC15.8 (OUT); also elsewhere on the board
X3: IC15.13 (-IN), SV10.16
X3_S: IC15.14 (OUT); also elsewhere on the board
X4: IC16.2 (-IN), SV10.20
X4_S: IC16.1 (OUT); also elsewhere on the board
X5: IC16.6 (-IN), SV10.24
X5_S: IC16.7 (OUT); also elsewhere on the board
X6: IC16.9 (-IN), SV10.28
X6_S: IC16.8 (OUT); also elsewhere on the board
X7: IC16.13 (-IN), SV10.30
X7_S: IC16.14 (OUT); also elsewhere on the board
~NEX: SV09.28; also elsewhere on the board
~PSM: IC19.14 (OUT), SV09.30

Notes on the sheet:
TODO:
Battery supply for SRAM.

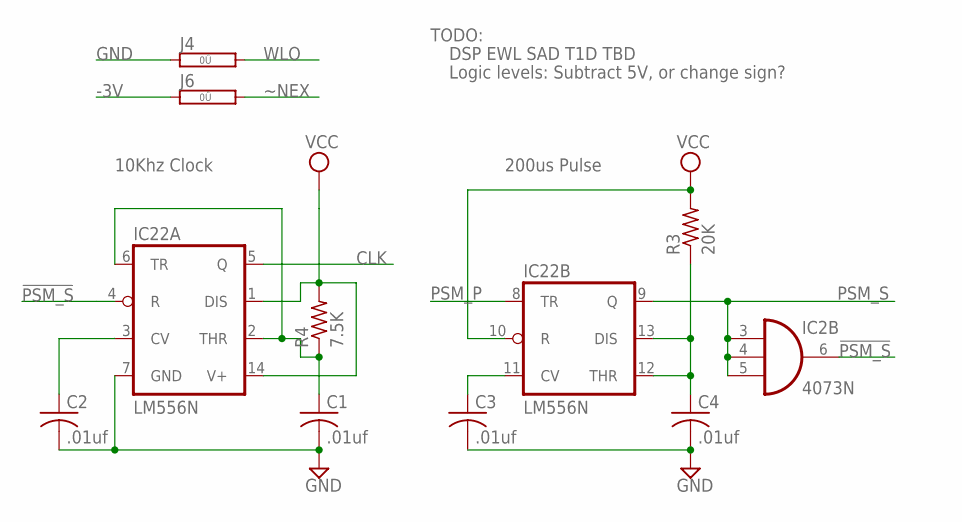
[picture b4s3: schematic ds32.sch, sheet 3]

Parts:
C1, C2, C3, C4: .01uf; C050-025X075
IC2: 4073N; DIL14
IC22: LM556N; DIL14
J4, J6: 0R; 0R/10
R3: 20K; 0207/10
R4: 7.5K; 0207/10

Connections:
!PSM_S: IC2.6 (O), IC22.4 (R); also elsewhere on the board
-3V: J6.1; also elsewhere on the board
CLK: IC22.5 (Q); also elsewhere on the board
GND: C1.2, C2.2, C3.2, C4.2, IC22.7 (GND), J4.1; also elsewhere on the board
unnamed: C1.1, IC22.2 (THR), IC22.6 (TR), R4.1
unnamed: C2.1, IC22.3 (CV)
unnamed: C4.1, IC22.12 (THR), IC22.13 (DIS), R3.1
unnamed: C3.1, IC22.11 (CV)
PSM_P: IC22.8 (TR); also elsewhere on the board
PSM_S: IC2.3 (I0), IC2.4 (I1), IC2.5 (I2), IC22.9 (Q)
VCC: IC22.1 (DIS), IC22.10 (R), IC22.14 (V+), R3.2, R4.2; also elsewhere on the board
VDD: IC2.14 (VDD); also elsewhere on the board
VSS: IC2.7 (VSS); also elsewhere on the board
WLO: J4.2; also elsewhere on the board
~NEX: J6.2; also elsewhere on the board

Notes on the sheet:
10Khz Clock
DSP EWL SAD T1D TBD
200us Pulse
TODO:
Logic levels: Subtract 5V, or change sign?
